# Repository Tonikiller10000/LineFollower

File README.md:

# LineFollower V5.0

## Description:

<table>
  <tr>
    <td>
    This is an robot made to follow a black line from start to finish for various competitions. 
    
It uses:
- ATmega328p-AU as an microcontroller(used in arduino uno);
- 16 or 20Mhz crystal resonator;
- [TB6612FNG](https://github.com/Tonikiller10000/MotorDriver_1) DC motor driver;
- [ITR8307-TR8](https://github.com/Tonikiller10000/ITR8307-TR8_SensorBar) sensor bar;
- LI-PO battery (7.2V)
- 2x DC motors with low torque high speed gear box
- robot suport (Wood, 3d printed or any low weight matherial)
    </td>
    <td></td>
  </tr>
</table>

 ## LineFollower V5.0
<table>
  <tr>
    <td></td>
    <td></td>
    <td></td>
  </tr>
</table>

 ## LineFollower V4.0(old design)
<table>
  <tr>
    <td></td>
    <td></td>
    <td></td>
  </tr>
</table>

### How it works:
The board is like a custom arduino UNO board powered from an 7.2V Li-Po battery trouth an 5V voltage regulator. The 8 analog pins are used as inputs from the sensor bar and 6 digital pins are used for the TB6612FNG motor driver witch is powered dirrectly from the battery to give more power to the motors. The reset pin has a 10K pullup resistor witch is pulled down by the reset button when it is pressed. The UART and ICSP pins wore pulled out to program the code and the bootloader of the IC.

### Programming:
[Programming of the robot](https://github.com/Tonikiller10000/LineFollower/blob/main/LineFollower_Pictures/w6.jpg): is done via UART protocoll with an [FTDI](https://github.com/Tonikiller10000/CH340G-FTDI-PROGRAMER) programming board. The code for the LineFollower is not ready. It uses the PID algorithm, and further documentation about this algorithm and the  source code for the robot will be posted this year.

### Start remote:

Robochalange remote:
[Start switch website](https://p1r.se/startmodule/)
[Start switch github](https://github.com/p1rse/robot-sumo-start-module/)
[IR Receiver Diode - TSOP38238](https://www.sparkfun.com/products/10266)
[schematic1](https://blogger.googleusercontent.com/img/b/R29vZ2xl/AVvXsEgnkNo1QEsxSPMNj7rN0opPGzlpkEMgxas9PnXUh-xvVR3l7UK27BbSvRroJmsxzwf3StBiDH0k4m-aEXX_4qJKeG5T4bKsfCBbcjgoykJYrBEhg5JI-Mr95yexPMCzkTw7kaGDIzET8ME/s1600/1235.png)
[schematic2](https://blogger.googleusercontent.com/img/b/R29vZ2xl/AVvXsEjLlN9CDAmP0rq2BlWM0Xdsypyy7NfGZpMYkufZPUAMmgCRdU-KhBC8AvPr7iOOQAwod2Hw66K_vuib1FNqDIHNemtnMvlSue2krN2hfp39g73NuTcx5fEXUF8i5MbJ3re-paKH2Z_Cgq0/s1600/1234.png)
[Q&A](https://robochallenge.ro/faq)
[MORE](https://destroyer3000.blogspot.com/2013/03/start-module-implement-yourself.html)

### How PID control work/`s

[Here](https://www.youtube.com/playlist?list=PLn8PRpmsu08pQBgjxYFXSsODEF3Jqmm-y) you can learn more about PID and under this you can see 
an analog linefollower project with and without PID:
- https://www.nutsvolts.com/magazine/article/the_pid_controller_part_1
- https://www.ecircuitcenter.com/Circuits/op_pid/op_pid.htm
- https://control.com/textbook/closed-loop-control/analog-electronic-pid-controllers/
- https://www.youtube.com/watch?v=4Y7zG48uHRo&list=PLOSOqCeZCHL0Qxb6YyrvGzjCg9FLfzHYJ

### ///////////////////////////////
- Small linefollower with op amp:https://www.youtube.com/watch?v=zZmvL0TkllI&list=WL&index=15&t=25s

### Design and mentions
[Robot support design considerations](https://github.com/Tonikiller10000/LineFollower/blob/main/LineFollower_Pictures/w3.png):
- to reach lower inertia, the components and the most of the mass of the robot should be placed on it\`s back;
- to reach a longer allowed response time from the sensor line detection to the mottor speed change it should be builted longer;
- to reach better torque on the wheels, it should be wider. 
- to mount the motors use molderd plastic motor holders, or be carefull when printing [it](https://github.com/Tonikiller10000/LineFollower/blob/main/LineFollower_Pictures/w1.jpg). 
- the case was made with autodesk fusion 360 at the 3d printer and with some M3 screws.

The next version will have the motor driver soldered on the board and motors screwed dirrectly to it as the suport. 
Another version will have a turbine for better torque and faster speeds.

## Links: 
- ATmega328p-AU (microcontroller): 
- LM78L05 (5V voltage regulator):
- Proof of work: https://github.com/Tonikiller10000/LineFollower/blob/main/LineFollower_Pictures/w2.mp4

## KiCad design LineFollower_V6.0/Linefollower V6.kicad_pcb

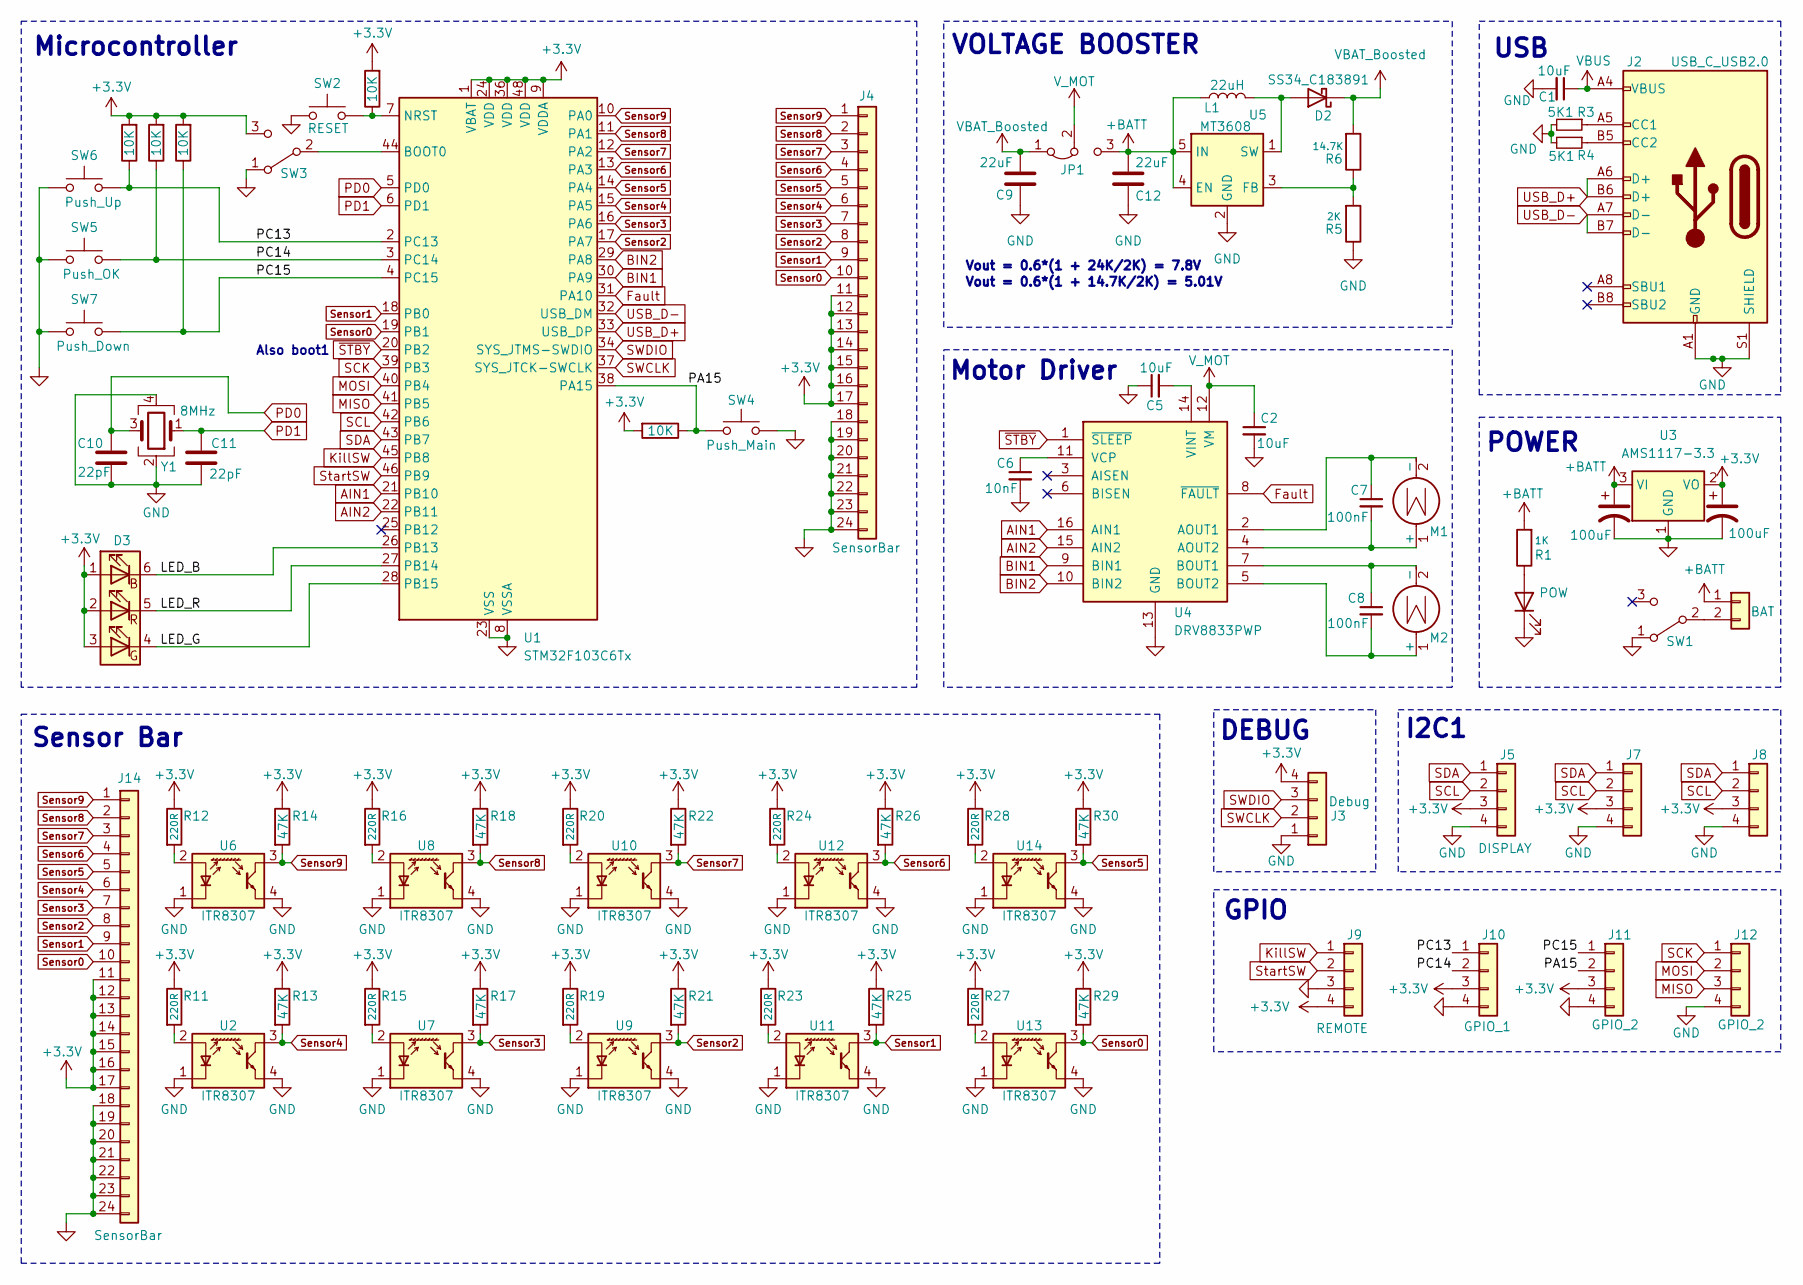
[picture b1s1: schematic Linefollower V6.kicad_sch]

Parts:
C1, C2, C5: 10uF; C_0603_1608Metric
C3, C4: 100uF; C_1210_3225Metric_Pad1.33x2.70mm_HandSolder
C6: 10nF; C_0603_1608Metric
C7, C8: 100nF; C_0603_1608Metric
C9, C12: 22uF
C10, C11: 22pF
D1: POW
D2: SS34_C183891
D3: SMLVN6RGB; LED_ROHM_SMLVN6
J1: BAT; PinHeader_1x02_P2.54mm_Vertical
J2: USB_C_USB2.0
J3: Debug; PinHeader_1x04_P2.54mm_Horizontal
J4, J14: SensorBar
J5, J7, J8: DISPLAY; PinHeader_1x04_P2.54mm_Vertical
J9: REMOTE; PinHeader_1x04_P2.54mm_Vertical
J10: GPIO_1; PinHeader_1x04_P2.54mm_Vertical
J11, J12: GPIO_2; PinHeader_1x04_P2.54mm_Vertical
JP1: Jumper_3_Bridged12
L1: 22uH; L_7.3x7.3_H4.5
M1, M2: Motor_DC; PinHeader_1x02_P2.54mm_Vertical
R1: 1K; R_1206_3216Metric
R2, R7, R8, R9, R10: 10K; R_1206_3216Metric
R3, R4: 5K1; R_0603_1608Metric
R5: 2K; R_0805_2012Metric_Pad1.20x1.40mm_HandSolder
R6: 14.7K; R_0805_2012Metric_Pad1.20x1.40mm_HandSolder
R11, R12, R15, R16, R19, R20, R23, R24, R27, R28: 220R; R_1206_3216Metric_Pad1.30x1.75mm_HandSolder
R13, R14, R17, R18, R21, R22, R25, R26, R29, R30: 47K; R_1206_3216Metric_Pad1.30x1.75mm_HandSolder
SW1, SW3: SW_SPDT
SW2: RESET
SW4: Push_Main
SW5: Push_OK
SW6: Push_Up
SW7: Push_Down
U1: STM32F103C6Tx; LQFP-48_7x7mm_P0.5mm
U2, U6, U7, U8, U9, U10, U11, U12, U13, U14: ITR8307; Everlight_ITR8307
U3: AMS1117-3.3; SOT-223-3_TabPin2
U4: DRV8833PWP; HTSSOP-16-1EP_4.4x5mm_P0.65mm_EP3.4x5mm_Mask2.46x2.31mm_The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
U5: MT3608; SOT-23-6
Y1: 8MHz

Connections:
+3.3V: C4.1, D3.1 (BA), D3.2 (RA), D3.3 (GA), J3.4, J4.11, J4.12, J4.13, J4.14, J4.15, J4.16, J4.17, J5.3, J7.3, J8.3, J9.4, J10.3, J11.3, J14.11, J14.12, J14.13, J14.14, J14.15, J14.16, J14.17, R2.2, R7.2, R8.2, R9.2, R10.2, R11.1, R12.1, R13.1, R14.1, R15.1, R16.1, R17.1, R18.1, R19.1, R20.1, R21.1, R22.1, R23.1, R24.1, R25.1, R26.1, R27.1, R28.1, R29.1, R30.1, SW3.3 (C), U1.1 (VBAT), U1.9 (VDDA), U1.24 (VDD), U1.36 (VDD), U1.48 (VDD), U3.2 (VO)
+BATT: C3.1, C12.1, J1.1, JP1.3 (B), L1.1, R1.2, U3.3 (VI), U5.4 (EN), U5.5 (IN)
/LED_B: D3.6 (BK), U1.26 (PB13)
/LED_G: D3.4 (GK), U1.28 (PB15)
/LED_R: D3.5 (RK), U1.27 (PB14)
/PA15: J11.2, R10.1, SW4.1, U1.38 (PA15)
/PC13: J10.1, R7.1, SW6.2, U1.2 (PC13)
/PC14: J10.2, R8.1, SW5.2, U1.3 (PC14)
/PC15: J11.1, R9.1, SW7.2, U1.4 (PC15)
AIN1: U1.21 (PB10), U4.16 (AIN1)
AIN2: U1.22 (PB11), U4.15 (AIN2)
BIN1: U1.30 (PA9), U4.9 (BIN1)
BIN2: U1.29 (PA8), U4.10 (BIN2)
Fault: U1.31 (PA10), U4.8 (~FAULT)
GND: C1.2, C2.2, C3.2, C4.2, C5.1, C6.2, C9.1, C10.1, C11.1, C12.2, D1.1 (K), J2.A1 (GND), J2.B1 (GND), J2.S1 (SHIELD), J3.1, J4.18, J4.19, J4.20, J4.21, J4.22, J4.23, J4.24, J5.4, J7.4, J8.4, J9.3, J10.4, J11.4, J12.4, J14.18, J14.19, J14.20, J14.21, J14.22, J14.23, J14.24, R3.2, R4.2, R5.1, SW1.1 (A), SW2.2, SW3.1 (A), SW4.2, SW5.1, SW6.1, SW7.1, U1.8 (VSSA), U1.23 (VSS), U1.35 (VSS), U1.47 (VSS), U2.1 (K), U2.4 (E), U3.1 (GND), U4.13 (GND), U4.17 (GND), U5.2 (GND), U6.1 (K), U6.4 (E), U7.1 (K), U7.4 (E), U8.1 (K), U8.4 (E), U9.1 (K), U9.4 (E), U10.1 (K), U10.4 (E), U11.1 (K), U11.4 (E), U12.1 (K), U12.4 (E), U13.1 (K), U13.4 (E), U14.1 (K), U14.4 (E), Y1.2, Y1.4; also elsewhere on the board
KillSW: J9.1, U1.45 (PB8)
MISO: J12.3, U1.41 (PB5)
MOSI: J12.2, U1.40 (PB4)
unnamed: D1.2 (A), R1.1
unnamed: D2.2 (A), L1.2, U5.1 (SW)
unnamed: J1.2, SW1.2 (B)
unnamed: J2.A5 (CC1), R3.1
unnamed: J2.B5 (CC2), R4.1
unnamed: C7.2, M1.1 (+), U4.4 (AOUT2)
unnamed: C7.1, M1.2 (-), U4.2 (AOUT1)
unnamed: C8.2, M2.1 (+), U4.5 (BOUT2)
unnamed: C8.1, M2.2 (-), U4.7 (BOUT1)
unnamed: SW3.2 (B), U1.44 (BOOT0)
unnamed: R2.1, SW2.1, U1.7 (NRST)
unnamed: R11.2, U2.2 (A)
unnamed: C6.1, U4.11 (VCP)
unnamed: C5.2, U4.14 (VINT)
unnamed: R5.2, R6.1, U5.3 (FB)
unnamed: R12.2, U6.2 (A)
unnamed: R15.2, U7.2 (A)
unnamed: R16.2, U8.2 (A)
unnamed: R19.2, U9.2 (A)
unnamed: R20.2, U10.2 (A)
unnamed: R23.2, U11.2 (A)
unnamed: R24.2, U12.2 (A)
unnamed: R27.2, U13.2 (A)
unnamed: R28.2, U14.2 (A)
PD0: C10.2, U1.5 (PD0), Y1.3; also elsewhere on the board
PD1: C11.2, U1.6 (PD1), Y1.1; also elsewhere on the board
SCK: J12.1, U1.39 (PB3)
SCL: J5.2, J7.2, J8.2, U1.42 (PB6)
SDA: J5.1, J7.1, J8.1, U1.43 (PB7)
SWCLK: J3.2, U1.37 (SYS_JTCK-SWCLK)
SWDIO: J3.3, U1.34 (SYS_JTMS-SWDIO)
Sensor0: J4.10, J14.10, R29.2, U1.19 (PB1), U13.3 (C)
Sensor1: J4.9, J14.9, R25.2, U1.18 (PB0), U11.3 (C)
Sensor2: J4.8, J14.8, R21.2, U1.17 (PA7), U9.3 (C)
Sensor3: J4.7, J14.7, R17.2, U1.16 (PA6), U7.3 (C)
Sensor4: J4.6, J14.6, R13.2, U1.15 (PA5), U2.3 (C)
Sensor5: J4.5, J14.5, R30.2, U1.14 (PA4), U14.3 (C)
Sensor6: J4.4, J14.4, R26.2, U1.13 (PA3), U12.3 (C)
Sensor7: J4.3, J14.3, R22.2, U1.12 (PA2), U10.3 (C)
Sensor8: J4.2, J14.2, R18.2, U1.11 (PA1), U8.3 (C)
Sensor9: J4.1, J14.1, R14.2, U1.10 (PA0), U6.3 (C)
StartSW: J9.2, U1.46 (PB9)
USB_D+: J2.A6 (D+), J2.B6 (D+), U1.33 (USB_DP)
USB_D-: J2.A7 (D-), J2.B7 (D-), U1.32 (USB_DM)
VBAT_Boosted: C9.2, D2.1 (K), JP1.1 (A), R6.2
VBUS: C1.1, J2.A4 (VBUS)
V_MOT: C2.1, JP1.2 (C), U4.12 (VM)
~STBY: U1.20 (PB2), U4.1 (~SLEEP)

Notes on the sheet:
Motor Driver
Also boot1
Vout = 0.6*(1 + 24K/2K) = 7.8V
POWER
Sensor Bar
Microcontroller
I2C1
USB
VOLTAGE BOOSTER
GPIO
Vout = 0.6*(1 + 14.7K/2K) = 5.01V
DEBUG

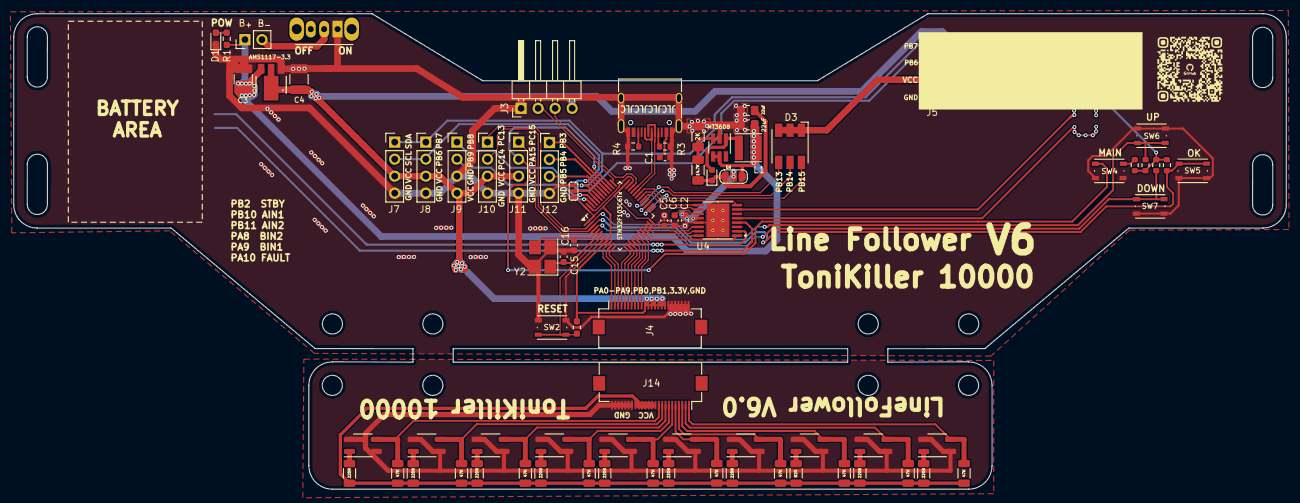
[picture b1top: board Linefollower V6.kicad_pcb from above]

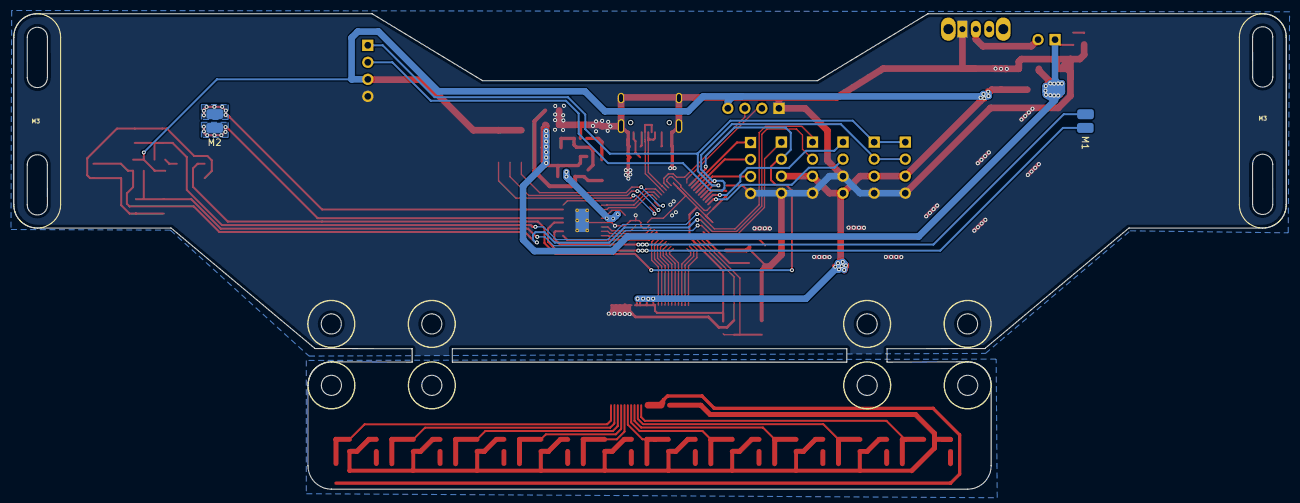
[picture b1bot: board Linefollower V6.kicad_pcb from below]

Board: 2 copper layers, 190.0 x 71.0 mm, 81 parts (2 on the bottom side), 66 nets.

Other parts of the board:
C15, C16: 22pF; C_0603_1608Metric
Y2: 8MHz; Crystal_SMD_3225-4Pin_3.2x2.5mm_HandSoldering

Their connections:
GND: C15.1, C16.1, Y2.2, Y2.4; also elsewhere on the board
PD0: C15.2, Y2.3; also elsewhere on the board
PD1: C16.2, Y2.1; also elsewhere on the board

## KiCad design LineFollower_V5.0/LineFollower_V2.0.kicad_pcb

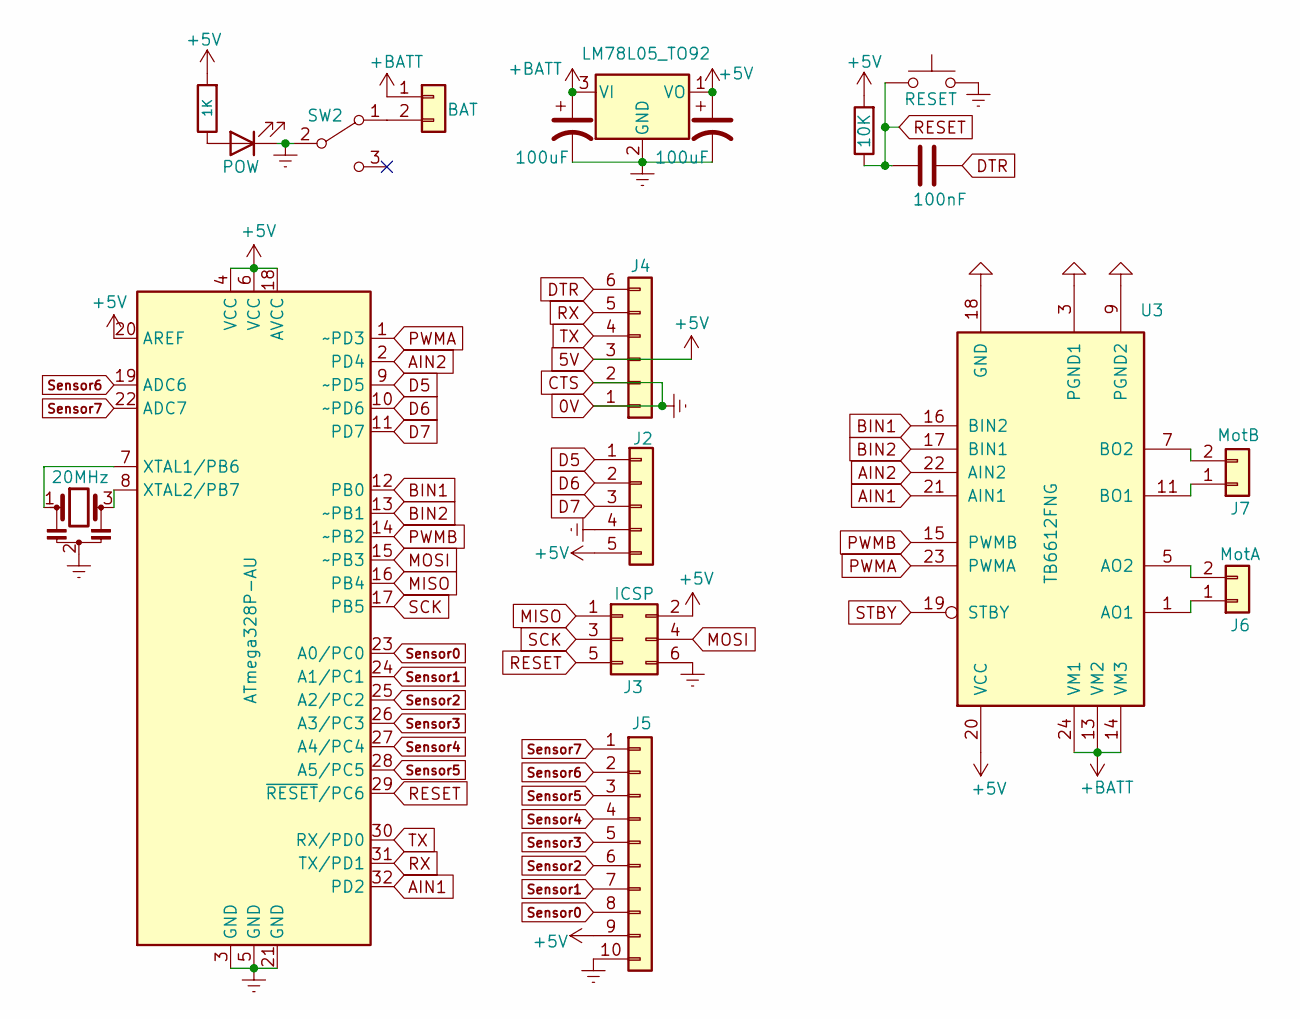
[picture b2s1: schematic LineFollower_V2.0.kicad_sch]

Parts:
C2, C3: 100uF; C_1210_3225Metric_Pad1.33x2.70mm_HandSolder
C6: 100nF; C_0805_2012Metric
D1: POW
J1: BAT; PinHeader_1x02_P2.54mm_Vertical
J2: Conn_01x05
J3: ICSP; PinHeader_2x03_P2.54mm_Vertical
J4: Conn_01x06_MountingPin
J5: Conn_01x10; PinHeader_1x10_P2.54mm_Horizontal
J6: MotA; PinHeader_1x02_P2.54mm_Vertical
J7: MotB; PinHeader_1x02_P2.54mm_Vertical
R1: 10K; R_1206_3216Metric
R2: 1K; R_1206_3216Metric
SW1: RESET
SW2: SW_SPDT
U1: ATmega328P-AU; TQFP-32_7x7mm_P0.8mm
U2: LM78L05_TO92; TO-92_Inline
U3: TB6612FNG; SSOP-24_5.3x8.2mm_P0.65mm
Y1: 20MHz; Resonator_SMD_Murata_CSTxExxV-3Pin_3.0x1.1mm

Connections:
0V: C2.2, C3.2, D1.1 (K), J2.4, J3.6, J4.1, J4.2, J5.10, SW1.2, SW2.2 (B), U1.3 (GND), U1.5 (GND), U1.21 (GND), U2.2 (GND), Y1.2; also elsewhere on the board
5V: C3.1, J2.5, J3.2, J4.3, J5.9, R1.2, R2.2, U1.4 (VCC), U1.6 (VCC), U1.18 (AVCC), U1.20 (AREF), U2.1 (VO), U3.20 (VCC); also elsewhere on the board
+BATT: C2.1, J1.1, U2.3 (VI), U3.13 (VM2), U3.14 (VM3), U3.24 (VM1); also elsewhere on the board
AIN1: U1.32 (PD2), U3.21 (AIN1); also elsewhere on the board
AIN2: U1.2 (PD4), U3.22 (AIN2); also elsewhere on the board
BIN1: U1.12 (PB0), U3.16 (BIN2); also elsewhere on the board
BIN2: U1.13 (~PB1), U3.17 (BIN1); also elsewhere on the board
D5: J2.1, U1.9 (~PD5)
D6: J2.2, U1.10 (~PD6)
D7: J2.3, U1.11 (PD7)
DTR: C6.1, J4.6
MISO: J3.1, U1.16 (PB4)
MOSI: J3.4, U1.15 (~PB3)
unnamed: D1.2 (A), R2.1
unnamed: J1.2, SW2.1 (A)
unnamed 15: J6.1, U3.1 (AO1), U3.2 (AO1); also elsewhere on the board
unnamed 16: J6.2, U3.5 (AO2), U3.6 (AO2); also elsewhere on the board
unnamed 17: J7.1, U3.11 (BO1), U3.12 (BO1); also elsewhere on the board
unnamed 18: J7.2, U3.7 (BO2), U3.8 (BO2); also elsewhere on the board
unnamed: U1.7 (XTAL1/PB6), Y1.1
unnamed: U1.8 (XTAL2/PB7), Y1.3
unnamed: U3.3 (PGND1), U3.4 (PGND1), U3.9 (PGND2), U3.10 (PGND2), U3.18 (GND)
PWMA: U1.1 (~PD3), U3.23 (PWMA); also elsewhere on the board
PWMB: U1.14 (~PB2), U3.15 (PWMB); also elsewhere on the board
RESET: C6.2, J3.5, R1.1, SW1.1, U1.29 (~RESET/PC6)
RX: J4.5, U1.31 (TX/PD1)
SCK: J3.3, U1.17 (PB5)
Sensor0: J5.8, U1.23 (A0/PC0)
Sensor1: J5.7, U1.24 (A1/PC1)
Sensor2: J5.6, U1.25 (A2/PC2)
Sensor3: J5.5, U1.26 (A3/PC3)
Sensor4: J5.4, U1.27 (A4/PC4)
Sensor5: J5.3, U1.28 (A5/PC5)
Sensor6: J5.2, U1.19 (ADC6)
Sensor7: J5.1, U1.22 (ADC7)
TX: J4.4, U1.30 (RX/PD0)

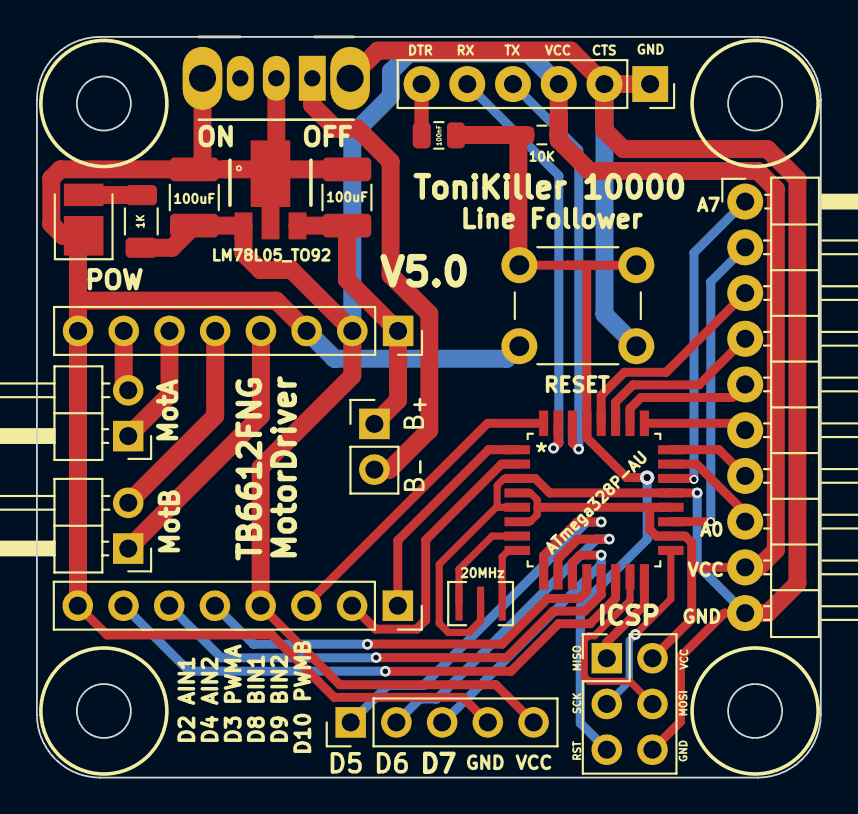
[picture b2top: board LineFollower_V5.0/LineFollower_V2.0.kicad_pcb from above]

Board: 2 copper layers, 43.5 x 41.2 mm, 20 parts (0 on the bottom side), 35 nets.

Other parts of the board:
J8: BAT; PinSocket_1x08_P2.54mm_Vertical
J9: Conn_01x03; PinSocket_1x08_P2.54mm_Vertical

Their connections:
0V: J8.3, J8.8, J9.8; also elsewhere on the board
5V: J8.2, J9.4; also elsewhere on the board
+BATT: J8.1; also elsewhere on the board
AIN1: J9.3; also elsewhere on the board
AIN2: J9.2; also elsewhere on the board
BIN1: J9.5; also elsewhere on the board
BIN2: J9.6; also elsewhere on the board
unnamed 15: J8.6; also elsewhere on the board
unnamed 16: J8.7; also elsewhere on the board
unnamed 17: J8.4; also elsewhere on the board
unnamed 18: J8.5; also elsewhere on the board
PWMA: J9.1; also elsewhere on the board
PWMB: J9.7; also elsewhere on the board

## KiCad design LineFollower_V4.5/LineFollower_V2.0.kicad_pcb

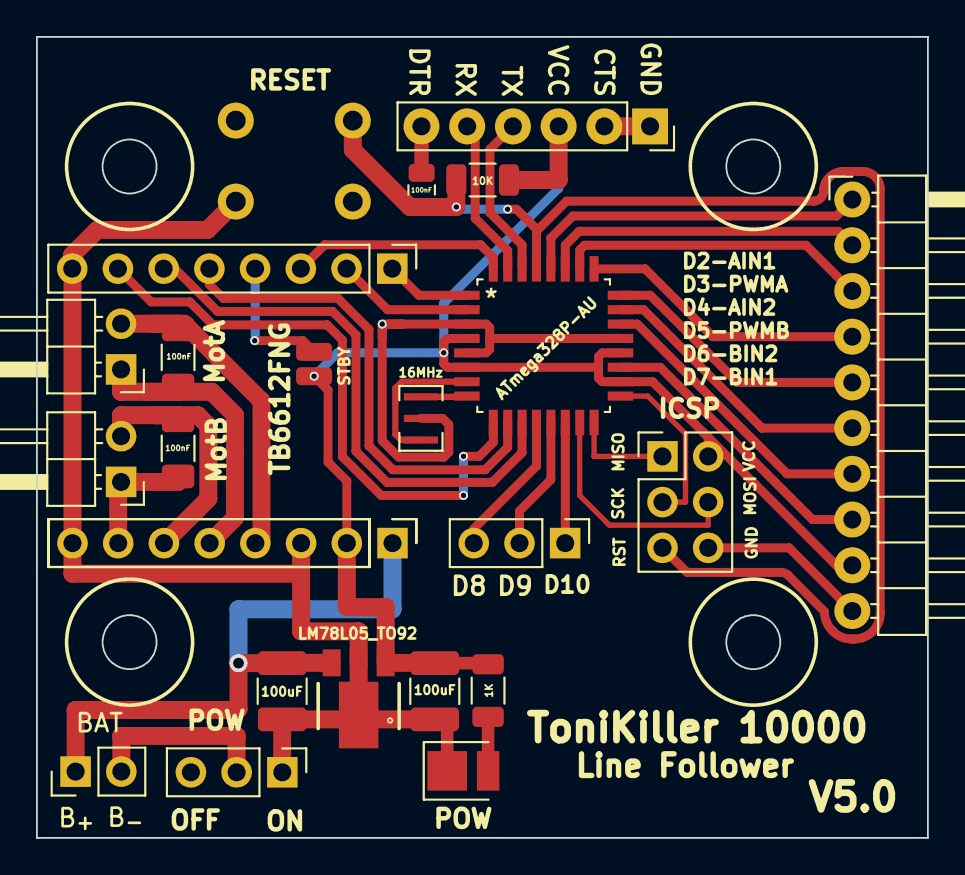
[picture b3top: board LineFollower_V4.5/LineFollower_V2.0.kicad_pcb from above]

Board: 2 copper layers, 49.5 x 44.5 mm, 21 parts (1 on the bottom side), 29 nets.

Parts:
C2, C3: 100uF; C_1210_3225Metric_Pad1.33x2.70mm_HandSolder
C4, C5: 100nF; C_1206_3216Metric_Pad1.33x1.80mm_HandSolder
C6: 100nF; C_0805_2012Metric
D1: POW; LED_PLCC_2835
J1: BAT; PinHeader_1x02_P2.54mm_Vertical
J3: ICSP; PinHeader_2x03_P2.54mm_Vertical
J4: Conn_01x06_MountingPin; PinSocket_1x06_P2.54mm_Vertical
J5: Conn_01x10; PinHeader_1x10_P2.54mm_Horizontal
J6: MotA; PinHeader_1x02_P2.54mm_Horizontal
J7: MotB; PinHeader_1x02_P2.54mm_Horizontal
R1: 10K; R_1206_3216Metric
R2: 1K; R_1206_3216Metric
SW1: RESET; SW_PUSH_6mm
SW2, SW4: POW; PinHeader_1x03_P2.54mm_Vertical
U1: ATmega328P-AU; TQFP32_32A_MCH
U2: LM78L05_TO92; PK(R-PSSO-F3)
U3: TB6612FNG; MotorDriver111
Y1: 16MHz; Resonator_SMD_Murata_CSTxExxV-3Pin_3.0x1.1mm

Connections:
0V: C2.2, C3.2, D1.1 (K), J3.6, J4.1, J4.2, J5.10, SW1.1, SW2.1, U1.3 (GND), U1.5 (GND), U1.21 (GND), U2.2 (GND), U3.8 (BO2), U3.9 (PGND2), U3.14 (VM3), Y1.2
5V: C3.1, J3.2, J4.3, J5.9, R1.2, R2.2, U1.4 (VCC), U1.6 (VCC), U1.18 (AVCC), U1.20 (AREF), U2.1 (VO), U3.4 (PGND1), U3.15 (PWMB)
10: SW4.1, U1.14 (~PB2)
+BATT: C2.1, J1.1, U2.3 (VI)
BIN1: U1.11 (PD7), U3.6 (AO2), U3.16 (BIN2)
BIN2: U1.10 (~PD6), U3.5 (AO2)
D8: SW4.3, U1.12 (PB0)
D9: SW4.2, U1.13 (~PB1)
DTR: C6.1, J4.6
MISO: J3.1, U1.16 (PB4)
MOSI: J3.4, U1.15 (~PB3)
unnamed: D1.2 (A), R2.1
unnamed: J1.2, SW2.2
unnamed: U3.1 (AO1), U3.2 (AO1)
unnamed: U1.7 (XTAL1/PB6), Y1.1
unnamed: U1.8 (XTAL2/PB7), Y1.3
PWMB: U1.9 (~PD5), U3.7 (BO2)
RESET: C6.2, J3.5, R1.1, SW1.2, U1.29 (~RESET/PC6)
RX: J4.5, U1.31 (TX/PD1)
SCK: J3.3, U1.17 (PB5)
Sensor0: J5.6, U1.23 (A0/PC0)
Sensor1: J5.5, U1.24 (A1/PC1)
Sensor2: J5.4, U1.25 (A2/PC2)
Sensor3: J5.3, U1.26 (A3/PC3)
Sensor4: J5.2, U1.27 (A4/PC4)
Sensor5: J5.1, U1.28 (A5/PC5)
Sensor6: J5.8, U1.19 (ADC6)
Sensor7: J5.7, U1.22 (ADC7)
TX: J4.4, U1.30 (RX/PD0)

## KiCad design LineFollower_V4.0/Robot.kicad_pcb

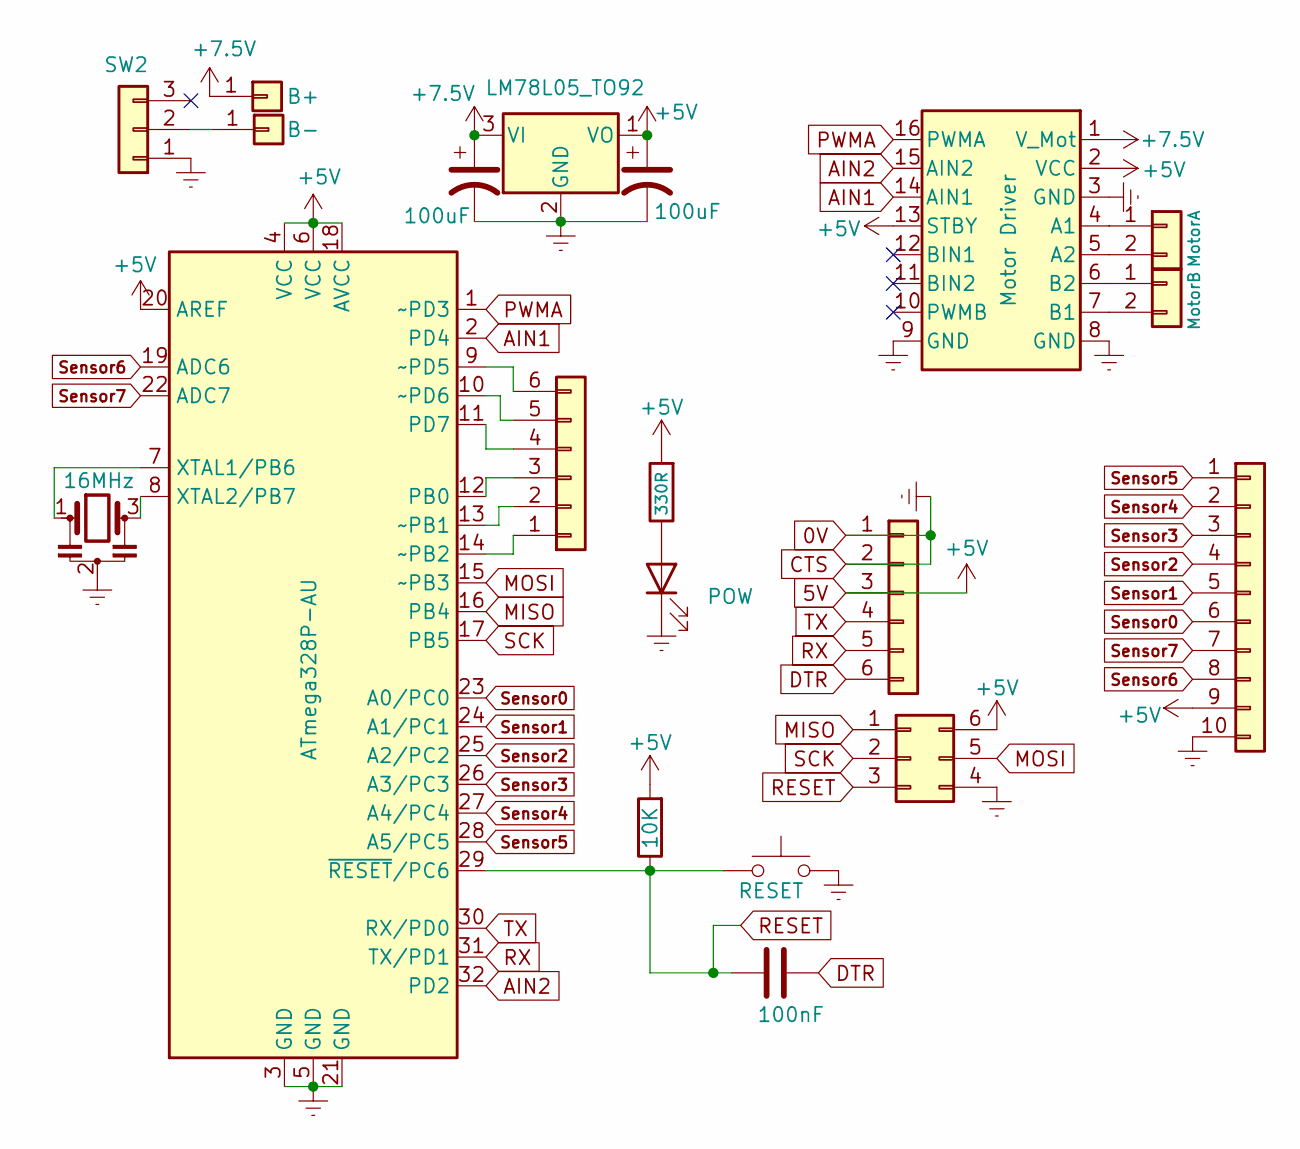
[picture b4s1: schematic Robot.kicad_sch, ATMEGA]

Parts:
C1, C2: 100uF
C3: 100nF
D1: POW
J1: Conn_01x06_MountingPin
J2: ICSP
J3: MotorA
J4: MotorB
J5: Conn_01x10
J6: Digital PINS
J8: B+
J9: B-
R1: 10K
R2: 330R
SW1: RESET
SW2: POW
U1: ATmega328P-AU; TQFP-32_7x7mm_P0.8mm
U2: LM78L05_TO92; TO-92_Inline
U3: Motor Driver; MotorDriver111
Y1: 16MHz

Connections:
0V: C1.2, C2.2, D1.1 (K), J1.1, J1.2, J2.4, J5.10, SW1.1, SW2.1, U1.3 (GND), U1.5 (GND), U1.21 (GND), U2.2 (GND), U3.3 (GND), U3.8 (GND), U3.9 (GND), Y1.2
5V: C2.1, J1.3, J2.6, J5.9, R1.2, R2.2, U1.4 (VCC), U1.6 (VCC), U1.18 (AVCC), U1.20 (AREF), U2.1 (VO), U3.2 (VCC), U3.13 (STBY)
+7.5V: C1.1, J8.1, U2.3 (VI), U3.1 (V_Mot)
AIN1: U1.2 (PD4), U3.14 (AIN1)
AIN2: U1.32 (PD2), U3.15 (AIN2)
DTR: C3.1, J1.6
MISO: J2.1, U1.16 (PB4)
MOSI: J2.5, U1.15 (~PB3)
unnamed: D1.2 (A), R2.1
unnamed: J3.1, U3.4 (A1)
unnamed: J3.2, U3.5 (A2)
unnamed: J4.1, U3.6 (B2)
unnamed: J4.2, U3.7 (B1)
unnamed: J9.1, SW2.2
unnamed: U1.7 (XTAL1/PB6), Y1.1
unnamed: U1.8 (XTAL2/PB7), Y1.3
unnamed: J6.6, U1.9 (~PD5)
unnamed: J6.5, U1.10 (~PD6)
unnamed: J6.4, U1.11 (PD7)
unnamed: J6.3, U1.12 (PB0)
unnamed: J6.2, U1.13 (~PB1)
unnamed: J6.1, U1.14 (~PB2)
PWMA: U1.1 (~PD3), U3.16 (PWMA)
RESET: C3.2, J2.3, R1.1, SW1.2, U1.29 (~RESET/PC6)
RX: J1.5, U1.31 (TX/PD1)
SCK: J2.2, U1.17 (PB5)
Sensor0: J5.6, U1.23 (A0/PC0)
Sensor1: J5.5, U1.24 (A1/PC1)
Sensor2: J5.4, U1.25 (A2/PC2)
Sensor3: J5.3, U1.26 (A3/PC3)
Sensor4: J5.2, U1.27 (A4/PC4)
Sensor5: J5.1, U1.28 (A5/PC5)
Sensor6: J5.8, U1.19 (ADC6)
Sensor7: J5.7, U1.22 (ADC7)
TX: J1.4, U1.30 (RX/PD0)

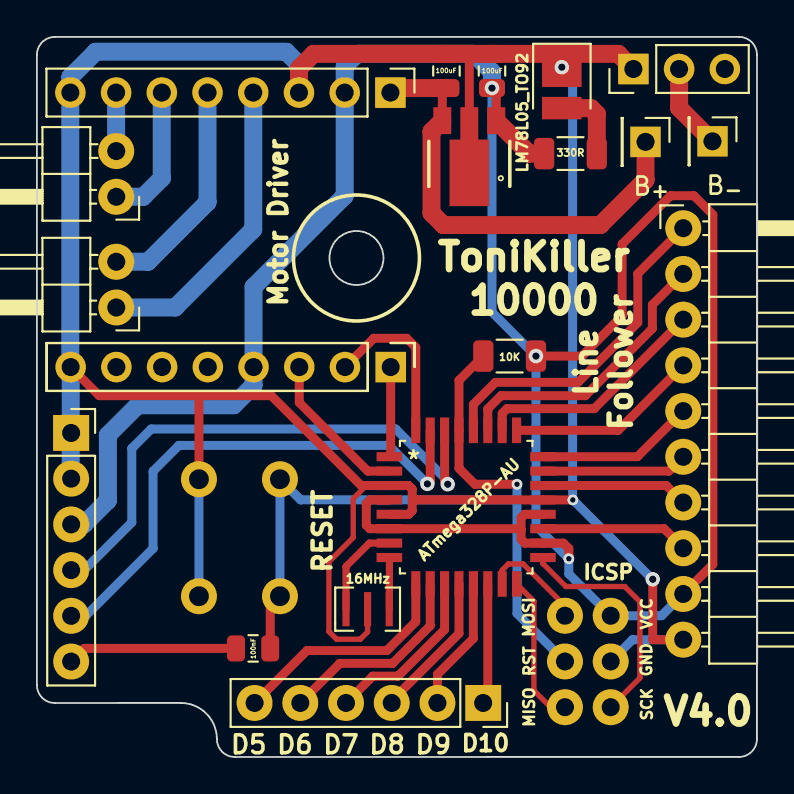
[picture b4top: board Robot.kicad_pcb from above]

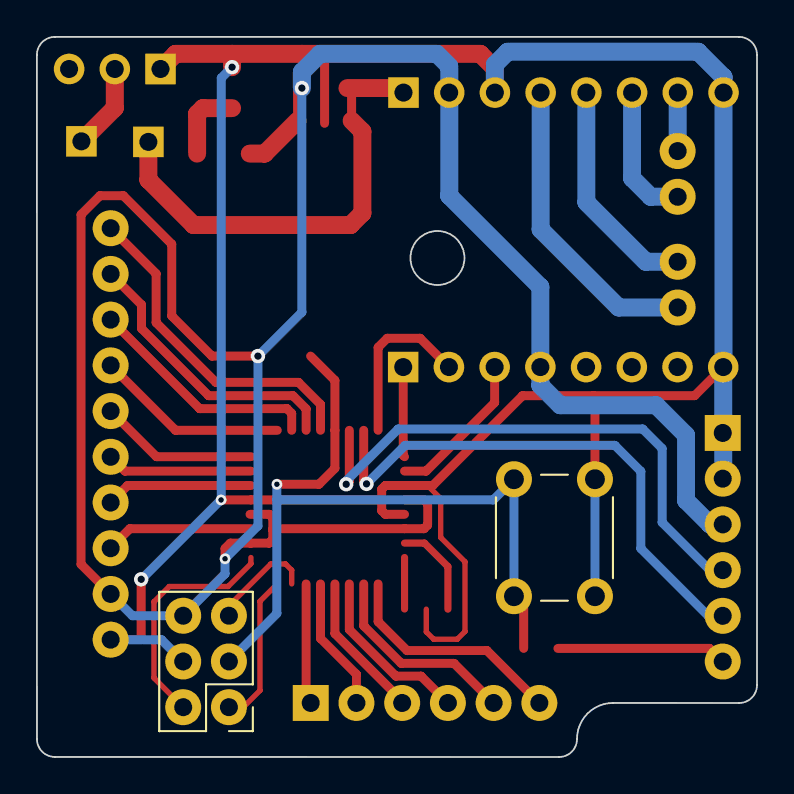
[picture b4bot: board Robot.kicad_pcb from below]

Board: 2 copper layers, 40.0 x 40.0 mm, 20 parts (2 on the bottom side), 35 nets.

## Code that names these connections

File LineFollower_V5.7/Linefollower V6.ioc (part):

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Mcu.Name=STM32F103C(4-6)Tx
Mcu.Package=LQFP48
Mcu.UserName=STM32F103C6Tx
PA0-WKUP.Signal=ADCx_IN0
PA1.Signal=ADCx_IN1
PA10.Signal=GPIO_Output
PA11.Mode=Device
PA11.Signal=USB_DM
PA12.Mode=Device
PA12.Signal=USB_DP
PA13.Mode=Serial_Wire
PA13.Signal=SYS_JTMS-SWDIO
PA14.Mode=Serial_Wire
PA14.Signal=SYS_JTCK-SWCLK
PA2.Signal=ADCx_IN2
PA3.Signal=ADCx_IN3
PA4.Signal=ADCx_IN4
PA5.Signal=ADCx_IN5
PA6.Signal=ADCx_IN6
PA7.Signal=ADCx_IN7
PA8.Signal=S_TIM1_CH1
PA9.Signal=S_TIM1_CH2
PB0.Signal=ADCx_IN8
PB1.Signal=ADCx_IN9
PB10.Signal=S_TIM2_CH3
PB11.Signal=S_TIM2_CH4
PB2.Signal=GPIO_Output
PB5.Signal=GPIO_Input
PB6.Signal=GPIO_Input
PB7.Signal=GPIO_Input
RCC.SYSCLKFreq_VALUE=48000000
RCC.SYSCLKSource=RCC_SYSCLKSOURCE_PLLCLK
board=custom

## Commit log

2024-02-24 upppd
2024-02-24 yryr
2024-02-24 ffff

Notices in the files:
parts and their libraries:
Copyright 2021 Accelerated Designs. All rights reserved.
